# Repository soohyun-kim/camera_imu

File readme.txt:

DEPRECATED: Project is no longer maintained; see evaluation report.  All material is outdated and is preserved only for reference.

The correct procedures in using the camera and the board in conjunction:

1.)  Ensure that the power switch located in the lower half othe board is set to off (right position).  This ensures that the board and camera boot simultaneously as to allow for the PWM signal to be introduced during the camera's grace period.
2.)  Power on the camera.  This may be done either by simply plugging in the corded power supply to the board, or pressing the camera's power button (when on battery power).
3.)  Observe the LED.  A solid green indicates all systems ready, to enter sensor calibration automatically.  A flashing magenta indicates that the sensor has not been detected.  A flashing yellow indicates the absence of an SD card.
4.)  The sensor will automatically enter calibration, indicated by a flashing green.  Do not touch the rig until flashing finishes.
5.)  Once calibration has finished, the LED will change to a solid blue, and the seven-segment display will now light on, indicating the number of record files created on the SD card.  The camera rig is now ready to record.
6.)  Record by pressing the RECORD button ONCE.  The LED will change to a solid red as indication.  Pressing it again will stop record.  Refer to the camera manual for general operation of the camera.
7.)  Press and HOLD the UNFREEZE button to initiate camera motion, and release when motion is finished.  This is to ensure that the corresponding virtual camera does not drift while the real counterpart remains motionless.
8.)  If sensor recalibration is needed, power cycle the board (use the power switch).  Do not power down the camera.

DO NOT:

	- Power the camera with the board's power switch in the OFF position.
	- Recalibrate the sensor without at least one REC start/stop cycle completed.

Engineering notes:

I still am not in full understanding of the PWM specs of this camera; there isn't much documentation for it at all.  Apparently it's tailored for that of servos which, according to Wikipedia, works in a way such that the absolute pulse width duration is only important, not the duty cycle; I dread experimenting with such a configuration.

In the current code it is written such that the PWM frequency is set to 50 Hz (the traditional servo frequency), and record start triggers when the standby duty cycle value of 51 (range 0-255, uint8, corresponding to 0-100% duty cycle) crosses a threshold value of 52 to end on 53; inversely, record stops on descent from 53 crossing 52 to 51.  This is the most reliable method discovered by my own experimentation.  This change cannot be abrupt; an immediate change between the two end values will not be registered by the camera.  The duty cycle value must lie on 52 for a finite duration of time; this is implemented as such in the code.

Further complicating the process is BlackMagic's decision to have the REC start/stop control accept a simple "switch" signal as well as a PWM signal.  In BlackMagic fashion, this is also little-documented, but experimentation revealed that REC start/stop toggles on a falling edge to ground.  This is problematic, as an independent power cycle of the Teensy temporarily drives all digital outputs low, which is then interpreted by the camera as a record toggle.  Simply put: a sensor recalibration results in an undesirable record toggle and subsequent index mismatching of the footage file and the camera rotation file.

This dual-purpose control creates complications in PWM mode as well.  The manual states (as one of the very few details listed about the specs) that the camera first operates in switch mode, expecting a switch input, until a PWM signal is detected, after which only the PWM signal is accepted; to return to switch mode, the camera must be power cycled.  Unfortunately, this results in the camera erronously interpreting the very first falling edge of the PWM signal as a switch toggle; only after is the PWM signal acknowledged.  In following, the camera always starts record at board startup, the instant the PWM signal is detected.

A workaround to this complication was quickly conceived when, following more experimentation, it was discovered that the camera has a brief "grace period" upon startup, when the SD card is acknowledged and characterized, in which external REC signals are ignored; introducing the PWM signal during this period will not trigger a REC start.  So, the code is written to introduce the PWM signal during this grace period, and it appears to work well...

...except on one condition.  A rather bizarre behavior, the camera only fully characterizes the PWM signal once one REC start/stop cycle has been completed in the defined fashion.  Only after at least one REC start/stop cycle has been administered does the camera fully "understand" the nature of the command and trigger record in the desired behavior, even when independently power cycling the board.  Failure to do this will result in the camera somehow entering record upon reboot of the Teensy after a power cycle.  Again - very bizarre and I fail to understand it in the slightest way...

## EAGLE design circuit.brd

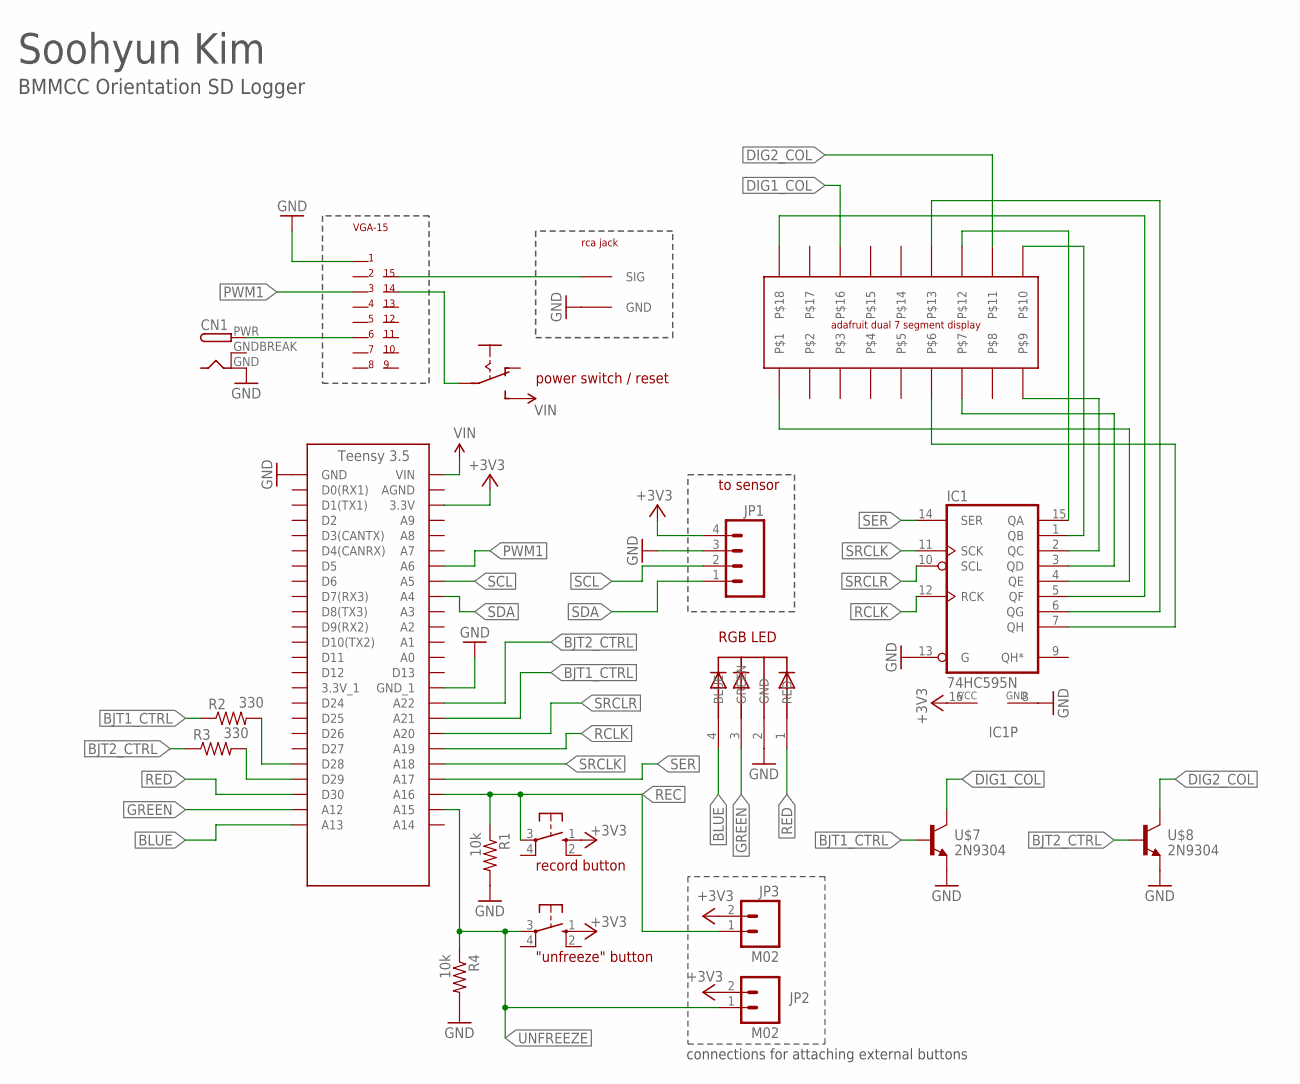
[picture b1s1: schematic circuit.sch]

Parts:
CN1: DCBARRELPTH; DCJACK_2MM_PTH
IC1: 74HC595N; DIL16
JP1: M04; 1X04
JP2, JP3: M02; 1X02
R1, R4: 10k; AXIAL-0.4
R2, R3: 330; AXIAL-0.4
S3, S4: 40-XX; B3F-40XX
U$1: TEENSY_3.5; TEENSY_3.5_SIMPLE
U$2: VGA-15
U$3: RCA
U$4: LED_5MM_RGB
U$5: SLIDE_SWITCH
U$6: DUAL_7SEG_DISPLAY
U$7, U$8: 2N9304; TO92

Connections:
+3V3: IC1.16 (VCC), JP1.4, JP2.2, JP3.2, S3.1 (S), S4.1 (S), U$1.3.3V
BJT1_CTRL: R2.P$1 (1), U$1.A21, U$7.2 (BASE)
BJT2_CTRL: R3.P$1 (1), U$1.A22, U$8.2 (BASE)
BLUE: U$1.A13, U$4.4 (BLUE)
D28: R2.P$2 (2), U$1.D28
D29: R3.P$2 (2), U$1.D29
DIG1_COL: U$6.16, U$7.1 (COLLECTOR)
DIG2_COL: U$6.11, U$8.1 (COLLECTOR)
GND: CN1.GND, IC1.8 (GND), IC1.13 (G), JP1.3, R1.P$2 (2), R4.P$2 (2), U$1.GND, U$1.GND_1, U$2.1, U$3.GND, U$4.2 (GND), U$7.3 (EMITTER), U$8.3 (EMITTER)
GNDBREAK: CN1.GNDBREAK
GREEN: U$1.A12, U$4.3 (GREEN)
unnamed: IC1.4 (QE), U$6.1
unnamed: U$2.14, U$5.P$2
unnamed: IC1.1 (QB), U$6.10
unnamed: IC1.2 (QC), U$6.9
unnamed: U$2.15, U$3.SIG
unnamed: CN1.PWR, U$2.6
unnamed: IC1.3 (QD), U$6.7
unnamed: IC1.15 (QA), U$6.12
unnamed: IC1.5 (QF), U$6.18
unnamed: IC1.6 (QG), U$6.13
unnamed: IC1.7 (QH), U$6.6
PWM1: U$1.A6, U$2.3
RCLK: IC1.12 (RCK), U$1.A19
REC: JP3.1, R1.P$1 (1), S3.3, U$1.A16
RED: U$1.D30, U$4.1 (RED)
SCL: JP1.2, U$1.A5
SDA: JP1.1, U$1.A4
SER: IC1.14 (SER), U$1.A17
SRCLK: IC1.11 (SCK), U$1.A18
SRCLR: IC1.10 (SCL), U$1.A20
UNFREEZE: JP2.1, R4.P$1 (1), S4.3, U$1.A15
VIN: U$1.VIN, U$5.P$3 (S)

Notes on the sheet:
RGB LED
record button
"unfreeze" button
to sensor
BMMCC Orientation SD Logger
Soohyun Kim
connections for attaching external buttons
power switch / reset

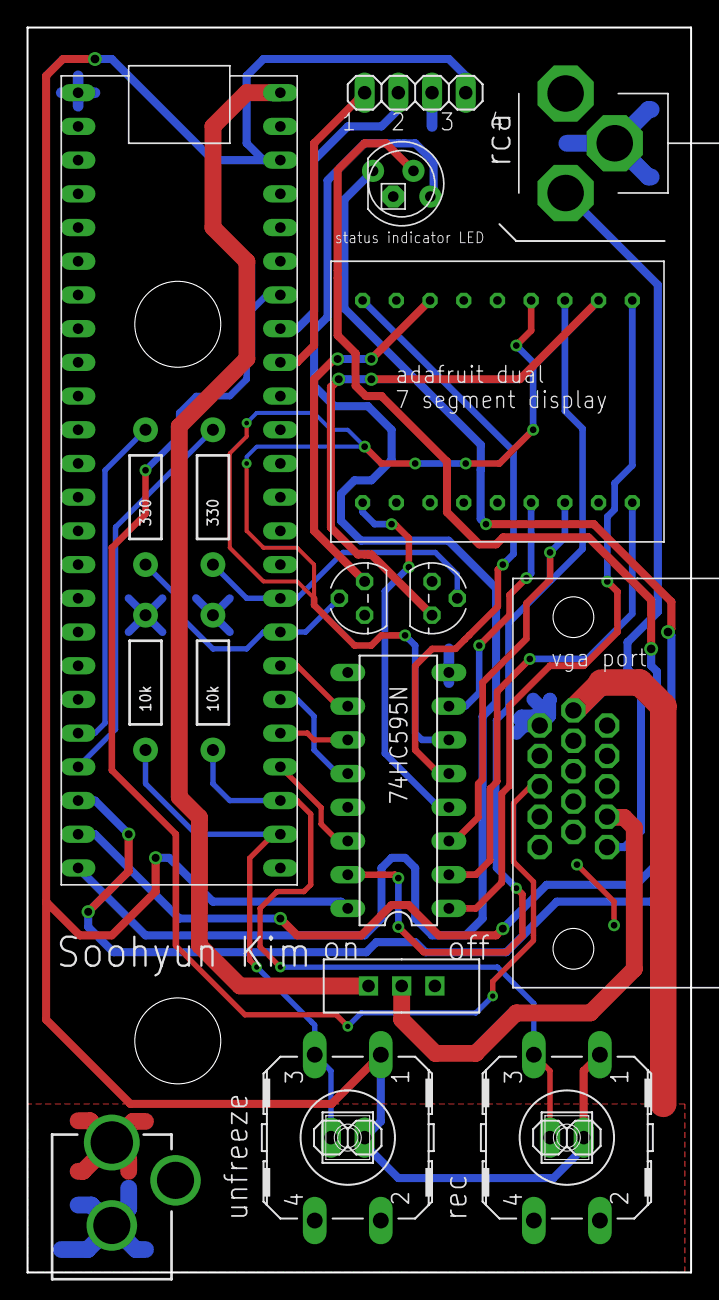
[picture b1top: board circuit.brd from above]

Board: 2 copper layers, 50.0 x 93.8 mm, 19 parts (0 on the bottom side), 32 nets.

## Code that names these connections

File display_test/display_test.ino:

#include <Metro.h>

bool flag;

Metro switcher = Metro(10);
Metro incrementer = Metro(500);

int number;

void setup() {
  // put your setup code here, to run once:
  pinMode(28, OUTPUT);  // bjt digit 1
  pinMode(29, OUTPUT);  // bjt digit 2

  pinMode(36, OUTPUT);  // ser data
  pinMode(37, OUTPUT);  // srclk
  pinMode(38, OUTPUT);  // rclk
  pinMode(39, OUTPUT);  // srclr

  digitalWrite(37, LOW);
  digitalWrite(38, LOW);

  // clear data
  digitalWrite(39, LOW);
  delay(10);
  digitalWrite(39, HIGH);

  Serial.begin(9600);   
  flag = true;
}

void loop() {
  // put your main code here, to run repeatedly:
  if (switcher.check()) {
    flag = !flag;
    if (flag) {
      printDigit((number-(number%10))/10);
    }
    if (!flag) {
      printDigit(number%10);
    }
    digitalWrite(28, flag);
    digitalWrite(29, !flag);
  }
  
  if (incrementer.check()) {
    number++;
    if (number==100) {
      number = 0;
    }
  }
}

void printDigit(int digit) {
  switch (digit) {
    case 0:
      dataIn(false, 2);
      dataIn(true, 6);
      break;
    case 1:
      dataIn(false, 5);
      dataIn(true, 2);
      dataIn(false, 1);
      break;
    case 2:
      dataIn(true, 2);
      dataIn(false, 1);
      dataIn(true, 2);
      dataIn(false, 1);
      dataIn(true, 2);
      break;
    case 3:
      dataIn(true, 2);
      dataIn(false, 2);
      dataIn(true, 4);
      break;
    case 4:
      dataIn(true, 3);
      dataIn(false, 2);
      dataIn(true, 2);
      dataIn(false, 1);
      break;
    case 5:
      dataIn(true, 3);
      dataIn(false, 1);
      dataIn(true, 2);
      dataIn(false, 1);
      dataIn(true, 1);
      break;
    case 6:
      dataIn(true, 6);
      dataIn(false, 1);
      dataIn(true, 1);
      break;
    case 7:
      dataIn(false, 5);
      dataIn(true, 3);
      break;
    case 8:
      dataIn(true, 8);
      break;
    case 9:
      dataIn(true, 3);
      dataIn(false, 1);
      dataIn(true, 4);
      break;
  }
  digitalWrite(38, HIGH);
  digitalWrite(38, LOW);
}

void dataIn(bool state, int no) {
  digitalWrite(36, state);
  for (int i=0; i<no; i++) {
    digitalWrite(37, HIGH);
    delayMicroseconds(10);
    digitalWrite(37, LOW);
    delayMicroseconds(10);
  }
}

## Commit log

2021-08-03 added blender test script
2021-08-09 added gyroscope test code
2021-08-10 added sd card record functionality
2021-08-11 finished sd-card-to-blender workflow
2021-08-17 edits
2021-08-17 merged remote record code into main
2021-08-18 added schematic, successfully tested display
2021-08-19 merged display code into main code, added sch
2021-08-20 added board for main pcb
2021-08-26 final?
2021-08-27 final
2021-09-04 added blender camera parameters
2021-09-05 added clarification for recorded angles
2021-09-05 added conversion from intrinsic angles to extrinsic
2021-09-08 added discovery about vga cables
2021-09-11 turns out blender rotation is in intrinsic angles. also, removed y (roll component)
2021-09-15 fixed uninitiated record start on camera powerup
2021-09-15 final touches, readme add
2021-09-24 revision blender script, readme
2021-10-24 unfrozen while recording
2022-01-20 project ended, evaluation added
